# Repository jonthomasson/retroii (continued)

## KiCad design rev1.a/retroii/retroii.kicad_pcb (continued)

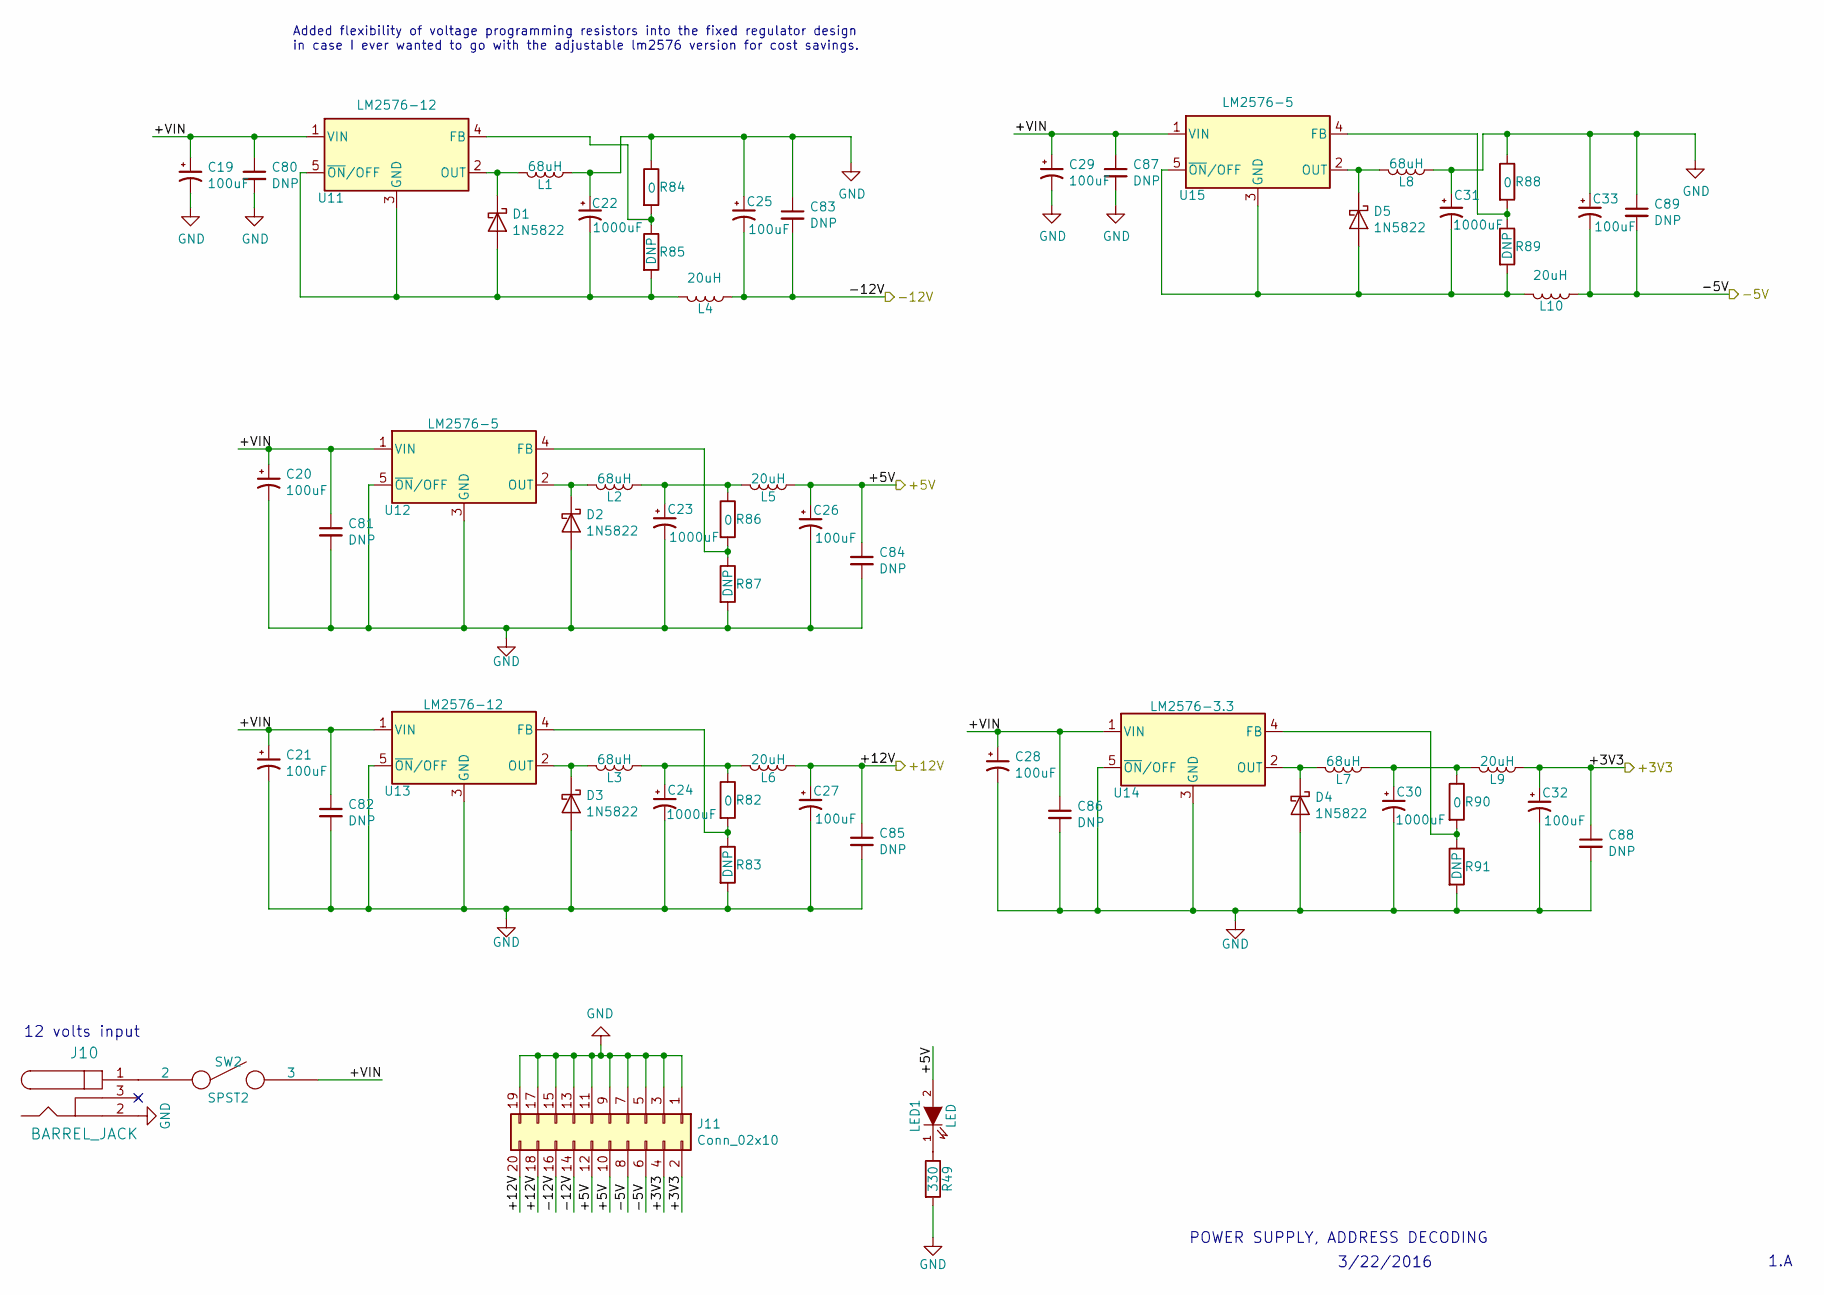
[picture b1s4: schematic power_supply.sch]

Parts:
C19, C20, C21, C25, C26, C27, C28, C29, C32, C33: 100uF; CP_Radial_D8.0mm_P3.50mm
C22, C23, C24, C30, C31: 1000uF; CP_Radial_D13.0mm_P5.00mm
C80, C81, C82, C83, C84, C85, C86, C87, C88, C89: DNP; C_Disc_D3.0mm_W2.0mm_P2.50mm
D1, D2, D3, D4, D5: 1N5822; D_DO-201AD_P15.24mm_Horizontal
J10: BARREL_JACK; Barrel_Jack_PJ002A
J11: Conn_02x10; PinSocket_2x10_P2.54mm_Vertical
L1, L2, L3, L7, L8: 68uH; Bourns_SRP1770TA-101M
L4, L5, L6, L9, L10: 20uH; Pulse_PF0382.223NLT
LED1: LED; WP1503CB_LED
R49: 330; R_Axial_DIN0207_L6.3mm_D2.5mm_P10.16mm_Horizontal
R82, R84, R86, R88, R90: 0; R_Axial_DIN0207_L6.3mm_D2.5mm_P10.16mm_Horizontal
R83, R85, R87, R89, R91: DNP; R_Axial_DIN0207_L6.3mm_D2.5mm_P10.16mm_Horizontal
SW2: SPST2; SW_Micro_Right_Angle_SPST
U11, U13: LM2576-12; TO-220-5_Horizontal_TabDown
U12, U15: LM2576-5; TO-220-5_Horizontal_TabDown
U14: LM2576-3.3; TO-220-5_Horizontal_TabDown

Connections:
/Address_Decoding/+5V: C26.1, C84.1, J11.10, J11.12, L5.1, LED1.2 (A); also elsewhere on the board
/Peripheral_IO/+12V: C27.1, C85.1, J11.18, J11.20, L6.1; also elsewhere on the board
/Peripheral_IO/-5V: C33.2, C89.2, J11.6, J11.8, L10.1; also elsewhere on the board
/Peripheral_IO/-12V: C25.2, C83.2, J11.14, J11.16, L4.1; also elsewhere on the board
/Power_Supply/+3V3: C32.1, C88.1, J11.2, J11.4, L9.1; also elsewhere on the board
/Power_Supply/+VIN: C19.1, C20.1, C21.1, C28.1, C29.1, C80.1, C81.1, C82.1, C86.1, C87.1, SW2.3, U11.1 (VIN), U12.1 (VIN), U13.1 (VIN), U14.1 (VIN), U15.1 (VIN)
GND: C19.2, C20.2, C21.2, C22.1, C23.2, C24.2, C25.1, C26.2, C27.2, C28.2, C29.2, C30.2, C31.1, C32.2, C33.1, C80.2, C81.2, C82.2, C83.1, C84.2, C85.2, C86.2, C87.2, C88.2, C89.1, D2.2 (A), D3.2 (A), D4.2 (A), J10.2, J11.1, J11.3, J11.5, J11.7, J11.9, J11.11, J11.13, J11.15, J11.17, J11.19, L1.1, L8.1, R49.2, R83.2, R84.1, R87.2, R88.1, R91.2, U12.3 (GND), U12.5 (~ON~/OFF), U13.3 (GND), U13.5 (~ON~/OFF), U14.3 (GND), U14.5 (~ON~/OFF); also elsewhere on the board
unnamed: C22.2, D1.2 (A), L4.2, R85.2, U11.3 (GND), U11.5 (~ON~/OFF)
unnamed: C23.1, L2.1, L5.2, R86.1
unnamed: C24.1, L3.1, L6.2, R82.1
unnamed: C30.1, L7.1, L9.2, R90.1
unnamed: C31.2, D5.2 (A), L10.2, R89.2, U15.3 (GND), U15.5 (~ON~/OFF)
unnamed: D1.1 (K), L1.2, U11.2 (OUT)
unnamed: D2.1 (K), L2.2, U12.2 (OUT)
unnamed: D3.1 (K), L3.2, U13.2 (OUT)
unnamed: D4.1 (K), L7.2, U14.2 (OUT)
unnamed: D5.1 (K), L8.2, U15.2 (OUT)
unnamed: LED1.1 (K), R49.1
unnamed: R82.2, R83.1, U13.4 (FB)
unnamed: R84.2, R85.1, U11.4 (FB)
unnamed: R86.2, R87.1, U12.4 (FB)
unnamed: R88.2, R89.1, U15.4 (FB)
unnamed: R90.2, R91.1, U14.4 (FB)

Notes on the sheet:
12 volts input
POWER SUPPLY, ADDRESS DECODING
3/22/2016
1.A
Added flexibility of voltage programming resistors into the fixed regulator design in case I ever wanted to go with the adjustable lm2576 version for cost savings.

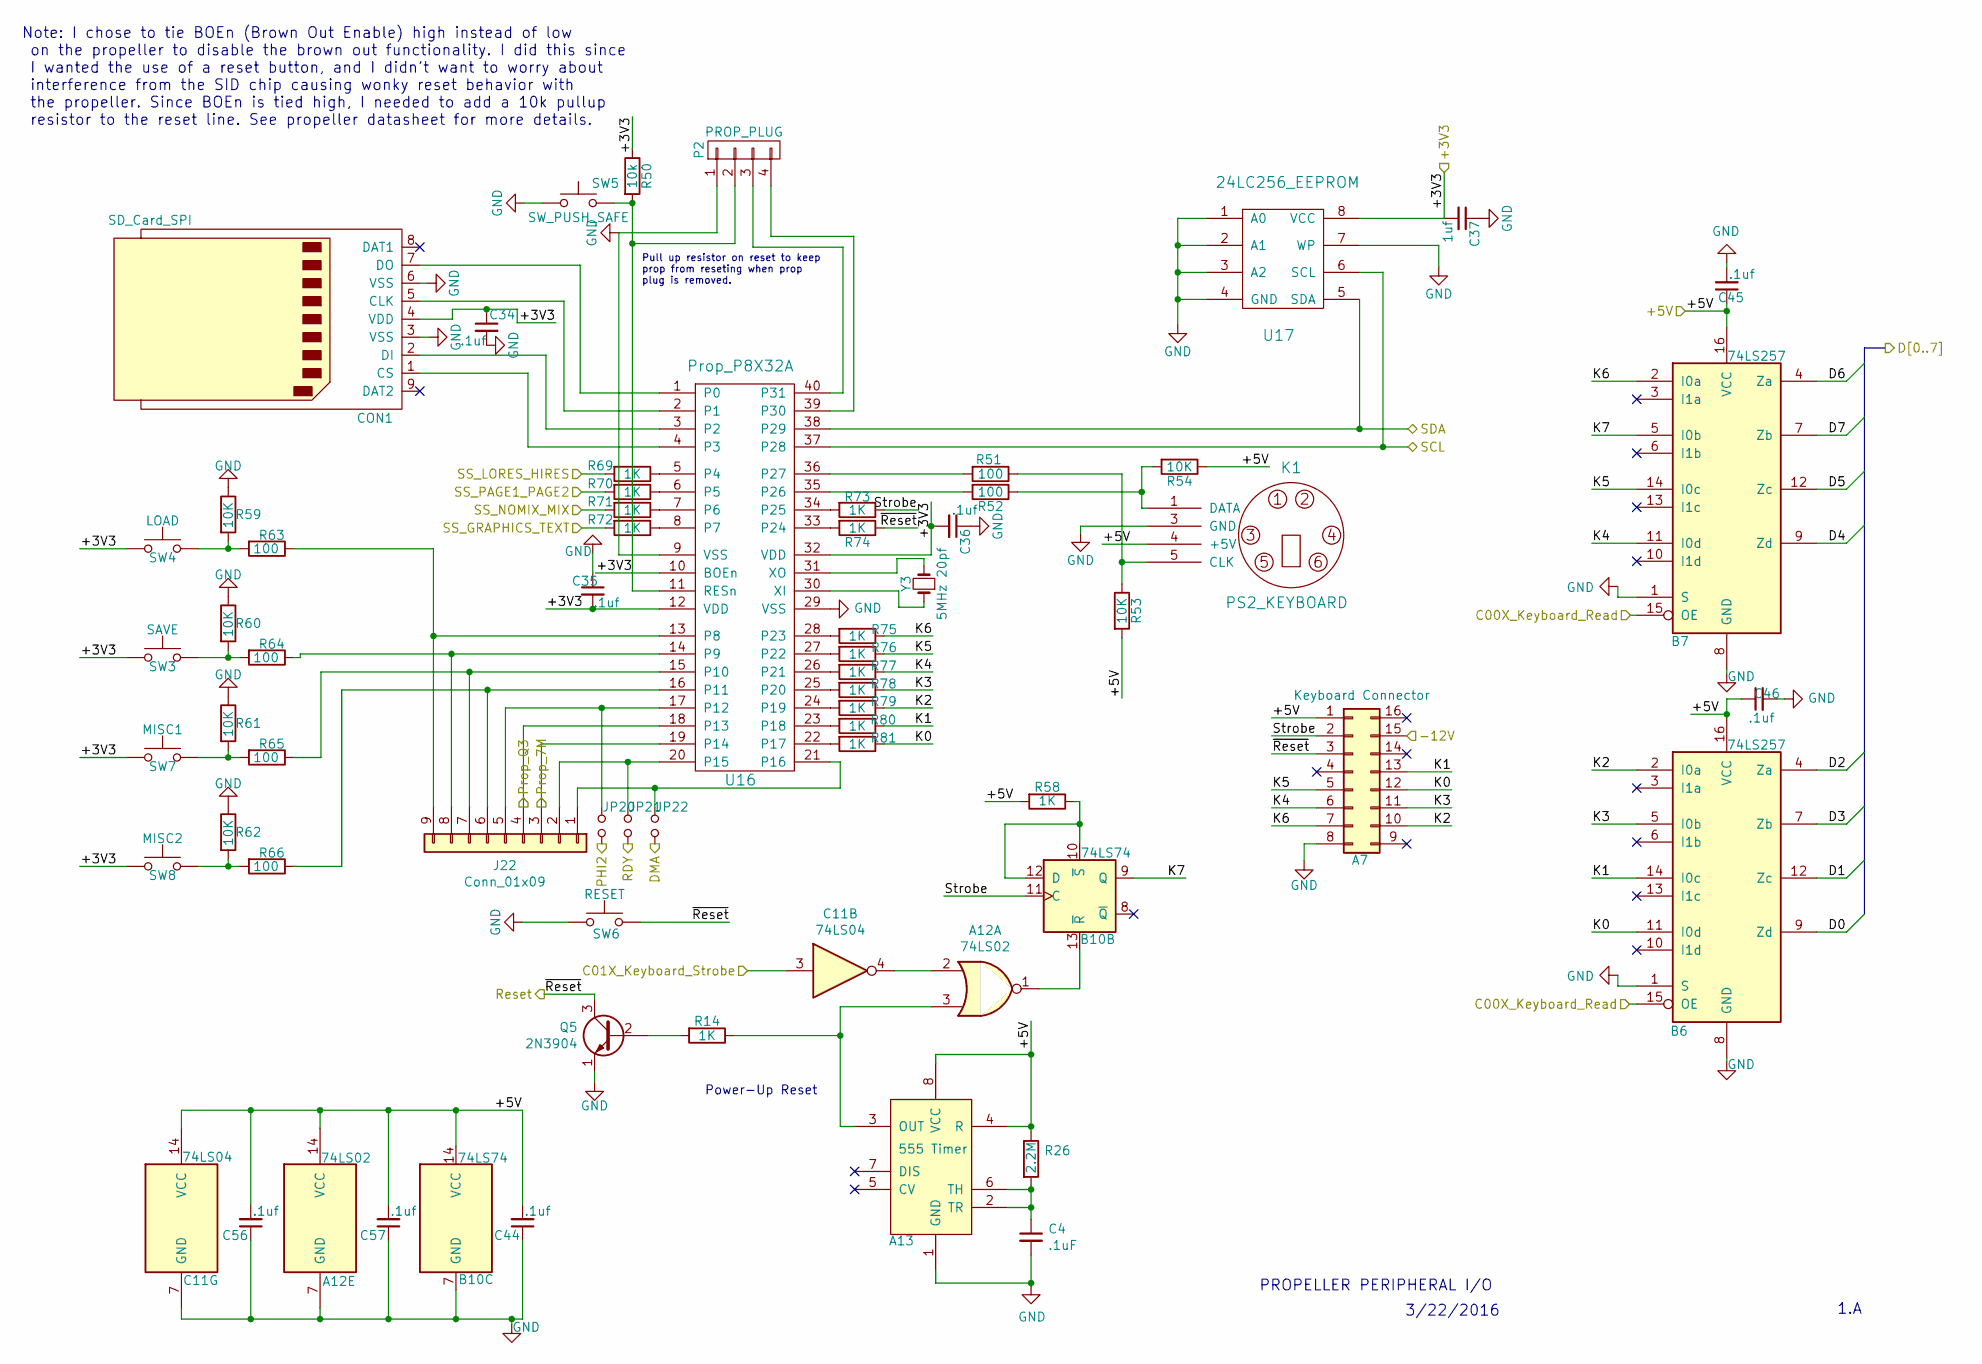
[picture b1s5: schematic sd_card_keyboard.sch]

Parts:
A7: Keyboard Connector; DIP-16_W7.62mm_Socket_LongPads
A12: 74LS02; DIP-14_W7.62mm_Socket_LongPads
A13: 555 Timer; DIP-8_W7.62mm_Socket_LongPads
B6, B7: 74LS257; DIP-16_W7.62mm_Socket_LongPads
B10: 74LS74; DIP-14_W7.62mm_Socket_LongPads
C4: .1uF; C_Disc_D3.0mm_W2.0mm_P2.50mm
C11: 74LS04; DIP-14_W7.62mm_Socket_LongPads
C34, C35, C36, C44, C45, C46, C56, C57: .1uf; C_Disc_D3.0mm_W2.0mm_P2.50mm
C37: 1uf; C_Disc_D4.7mm_W2.5mm_P5.00mm
CON1: SD_Card_SPI; DM1AASFPEJ_SDCARD
J22: Conn_01x09; PinSocket_1x09_P2.54mm_Vertical
JP20, JP21, JP22: Jumper_NO_Small; PinHeader_1x02_P2.54mm_Vertical
K1: PS2_KEYBOARD; MD60SM
P2: PROP_PLUG; PinHeader_1x04_P2.54mm_Vertical
Q5: 2N3904; TO-92_Inline
R14, R58, R69, R70, R71, R72, R73, R74, R75, R76, R77, R78, R79, R80, R81: 1K; R_Axial_DIN0207_L6.3mm_D2.5mm_P10.16mm_Horizontal
R26: 2.2M; R_Axial_DIN0207_L6.3mm_D2.5mm_P10.16mm_Horizontal
R50: 10k; R_Axial_DIN0207_L6.3mm_D2.5mm_P10.16mm_Horizontal
R51, R52, R63, R64, R65, R66: 100; R_Axial_DIN0207_L6.3mm_D2.5mm_P10.16mm_Horizontal
R53, R54, R59, R60, R61, R62: 10K; R_Axial_DIN0207_L6.3mm_D2.5mm_P10.16mm_Horizontal
SW3: SAVE; TE_Tactile_2-1825027-0
SW4: LOAD; TE_Tactile_2-1825027-0
SW5: SW_PUSH_SAFE; TE_1825910-6
SW6: RESET; TE_Tactile_2-1825027-0
SW7: MISC1; TE_Tactile_2-1825027-0
SW8: MISC2; TE_Tactile_2-1825027-0
U16: Prop_P8X32A; DIP-40_W15.24mm_Socket_LongPads
U17: 24LC256_EEPROM; DIP-8_W7.62mm_Socket_LongPads
Y3: 5MHz 20pf; crystal_hc-49s

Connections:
/Address_Decoding/+5V: A7.1, A12.14 (VCC), A13.4 (R), A13.8 (VCC), B6.16 (VCC), B7.16 (VCC), B10.14 (VCC), C11.14 (VCC), C44.2, C45.1, C46.1, C56.2, C57.2, K1.4 (+5V), R26.1, R53.2, R54.1, R58.2; also elsewhere on the board
/Address_Decoding/C00X_Keyboard_Read: B6.15 (OE), B7.15 (OE); also elsewhere on the board
/Address_Decoding/C01X_Keyboard_Strobe: C11.3; also elsewhere on the board
/Address_Decoding/PHI2: JP20.2; also elsewhere on the board
/Address_Decoding/SS_GRAPHICS_TEXT: R72.2; also elsewhere on the board
/Address_Decoding/SS_LORES_HIRES: R69.2; also elsewhere on the board
/Address_Decoding/SS_NOMIX_MIX: R71.2; also elsewhere on the board
/Address_Decoding/SS_PAGE1_PAGE2: R70.2; also elsewhere on the board
/CPU_RAM_ROM/D0: B6.9 (Zd); also elsewhere on the board
/CPU_RAM_ROM/D1: B6.12 (Zc); also elsewhere on the board
/CPU_RAM_ROM/D2: B6.4 (Za); also elsewhere on the board
/CPU_RAM_ROM/D3: B6.7 (Zb); also elsewhere on the board
/CPU_RAM_ROM/D4: B7.9 (Zd); also elsewhere on the board
/CPU_RAM_ROM/D5: B7.12 (Zc); also elsewhere on the board
/CPU_RAM_ROM/D6: B7.4 (Za); also elsewhere on the board
/CPU_RAM_ROM/DMA: JP22.2; also elsewhere on the board
/CPU_RAM_ROM/RDY: JP21.2; also elsewhere on the board
/CPU_RAM_ROM/RESB: A7.3, Q5.3 (C), R74.1, SW6.4; also elsewhere on the board
/Peripheral_IO/-12V: A7.15; also elsewhere on the board
/Peripheral_IO/Prop_7M: J22.3, U16.19 (P14); also elsewhere on the board
/Peripheral_IO/Prop_Q3: J22.4, U16.18 (P13); also elsewhere on the board
/Power_Supply/+3V3: C34.1, C35.2, C36.2, C37.2, CON1.4 (VDD), R50.1, SW3.1, SW4.1, SW7.1, SW8.1, U16.10 (BOEn), U16.12 (VDD), U16.32 (VDD), U17.8 (VCC); also elsewhere on the board
/SD_Card_And_Keyboard/K0: A7.12, B6.11 (I0d), R81.1
/SD_Card_And_Keyboard/K1: A7.13, B6.14 (I0c), R80.1
/SD_Card_And_Keyboard/K2: A7.10, B6.2 (I0a), R79.1
/SD_Card_And_Keyboard/K3: A7.11, B6.5 (I0b), R78.1
/SD_Card_And_Keyboard/K4: A7.6, B7.11 (I0d), R77.1
/SD_Card_And_Keyboard/K5: A7.5, B7.14 (I0c), R76.1
/SD_Card_And_Keyboard/K6: A7.7, B7.2 (I0a), R75.1
/SD_Card_And_Keyboard/K7: B7.5 (I0b), B10.9 (Q)
/SD_Card_And_Keyboard/SCL: U16.37 (P28), U17.6 (SCL); also elsewhere on the board
/SD_Card_And_Keyboard/SDA: U16.38 (P29), U17.5 (SDA); also elsewhere on the board
/SD_Card_And_Keyboard/Strobe: A7.2, B10.11 (C), R73.1
GND: A7.8, A12.7 (GND), A13.1 (GND), B6.1 (S), B6.8 (GND), B7.1 (S), B7.8 (GND), B10.7 (GND), C4.2, C11.7 (GND), C34.2, C35.1, C36.1, C37.1, C44.1, C45.2, C46.2, C56.1, C57.1, CON1.3 (VSS), CON1.6 (VSS), K1.3 (GND), P2.1, Q5.1 (E), R59.1, R60.1, R61.1, R62.1, SW5.1, SW6.1, U16.9 (VSS), U16.29 (VSS), U17.1 (A0), U17.2 (A1), U17.3 (A2), U17.4 (GND), U17.7 (WP); also elsewhere on the board
unnamed: A12.1, B10.13 (~R)
unnamed: A12.2, C11.4
unnamed: A12.3, A13.3 (OUT), R14.1
unnamed: A13.2 (TR), A13.6 (TH), C4.1, R26.2
unnamed: B10.10 (~S), B10.12 (D), R58.1
unnamed: CON1.1 (CS), U16.4 (P3)
unnamed: CON1.2 (DI), U16.3 (P2)
unnamed: CON1.5 (CLK), U16.2 (P1)
unnamed: CON1.7 (DO), U16.1 (P0)
unnamed: J22.1, JP22.1, U16.21 (P16)
unnamed: J22.2, JP21.1, U16.20 (P15)
unnamed: J22.5, JP20.1, U16.17 (P12)
unnamed: J22.6, R66.1, U16.16 (P11)
unnamed: J22.7, R65.1, U16.15 (P10)
unnamed: J22.8, R64.1, U16.14 (P9)
unnamed: J22.9, R63.1, U16.13 (P8)
unnamed: K1.1 (DATA), R52.1, R54.2
unnamed: K1.5 (CLK), R51.1, R53.1
unnamed: P2.2, R50.2, SW5.4, U16.11 (RESn)
unnamed: P2.3, U16.40 (P31)
unnamed: P2.4, U16.39 (P30)
unnamed: Q5.2 (B), R14.2
unnamed: R51.2, U16.36 (P27)
unnamed: R52.2, U16.35 (P26)
unnamed: R59.2, R63.2, SW4.4
unnamed: R60.2, R64.2, SW3.4
unnamed: R61.2, R65.2, SW7.4
unnamed: R62.2, R66.2, SW8.4
unnamed: R69.1, U16.5 (P4)
unnamed: R70.1, U16.6 (P5)
unnamed: R71.1, U16.7 (P6)
unnamed: R72.1, U16.8 (P7)
unnamed: R73.2, U16.34 (P25)
unnamed: R74.2, U16.33 (P24)
unnamed: R75.2, U16.28 (P23)
unnamed: R76.2, U16.27 (P22)
unnamed: R77.2, U16.26 (P21)
unnamed: R78.2, U16.25 (P20)
unnamed: R79.2, U16.24 (P19)
unnamed: R80.2, U16.23 (P18)
unnamed: R81.2, U16.22 (P17)
unnamed: U16.30 (XI), Y3.1
unnamed: U16.31 (XO), Y3.2

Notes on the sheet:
Note: I chose to tie BOEn (Brown Out Enable) high instead of low on the propeller to disable the brown out functionality. I did this since I wanted the use of a reset button, and I didn't want to worry about interference from the SID chip causing wonky reset behavior with the propeller. Since BOEn 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
Pull up resistor on reset to keep prop from reseting when prop plug is removed.
PROPELLER PERIPHERAL I/O
3/22/2016
1.A
Power-Up Reset

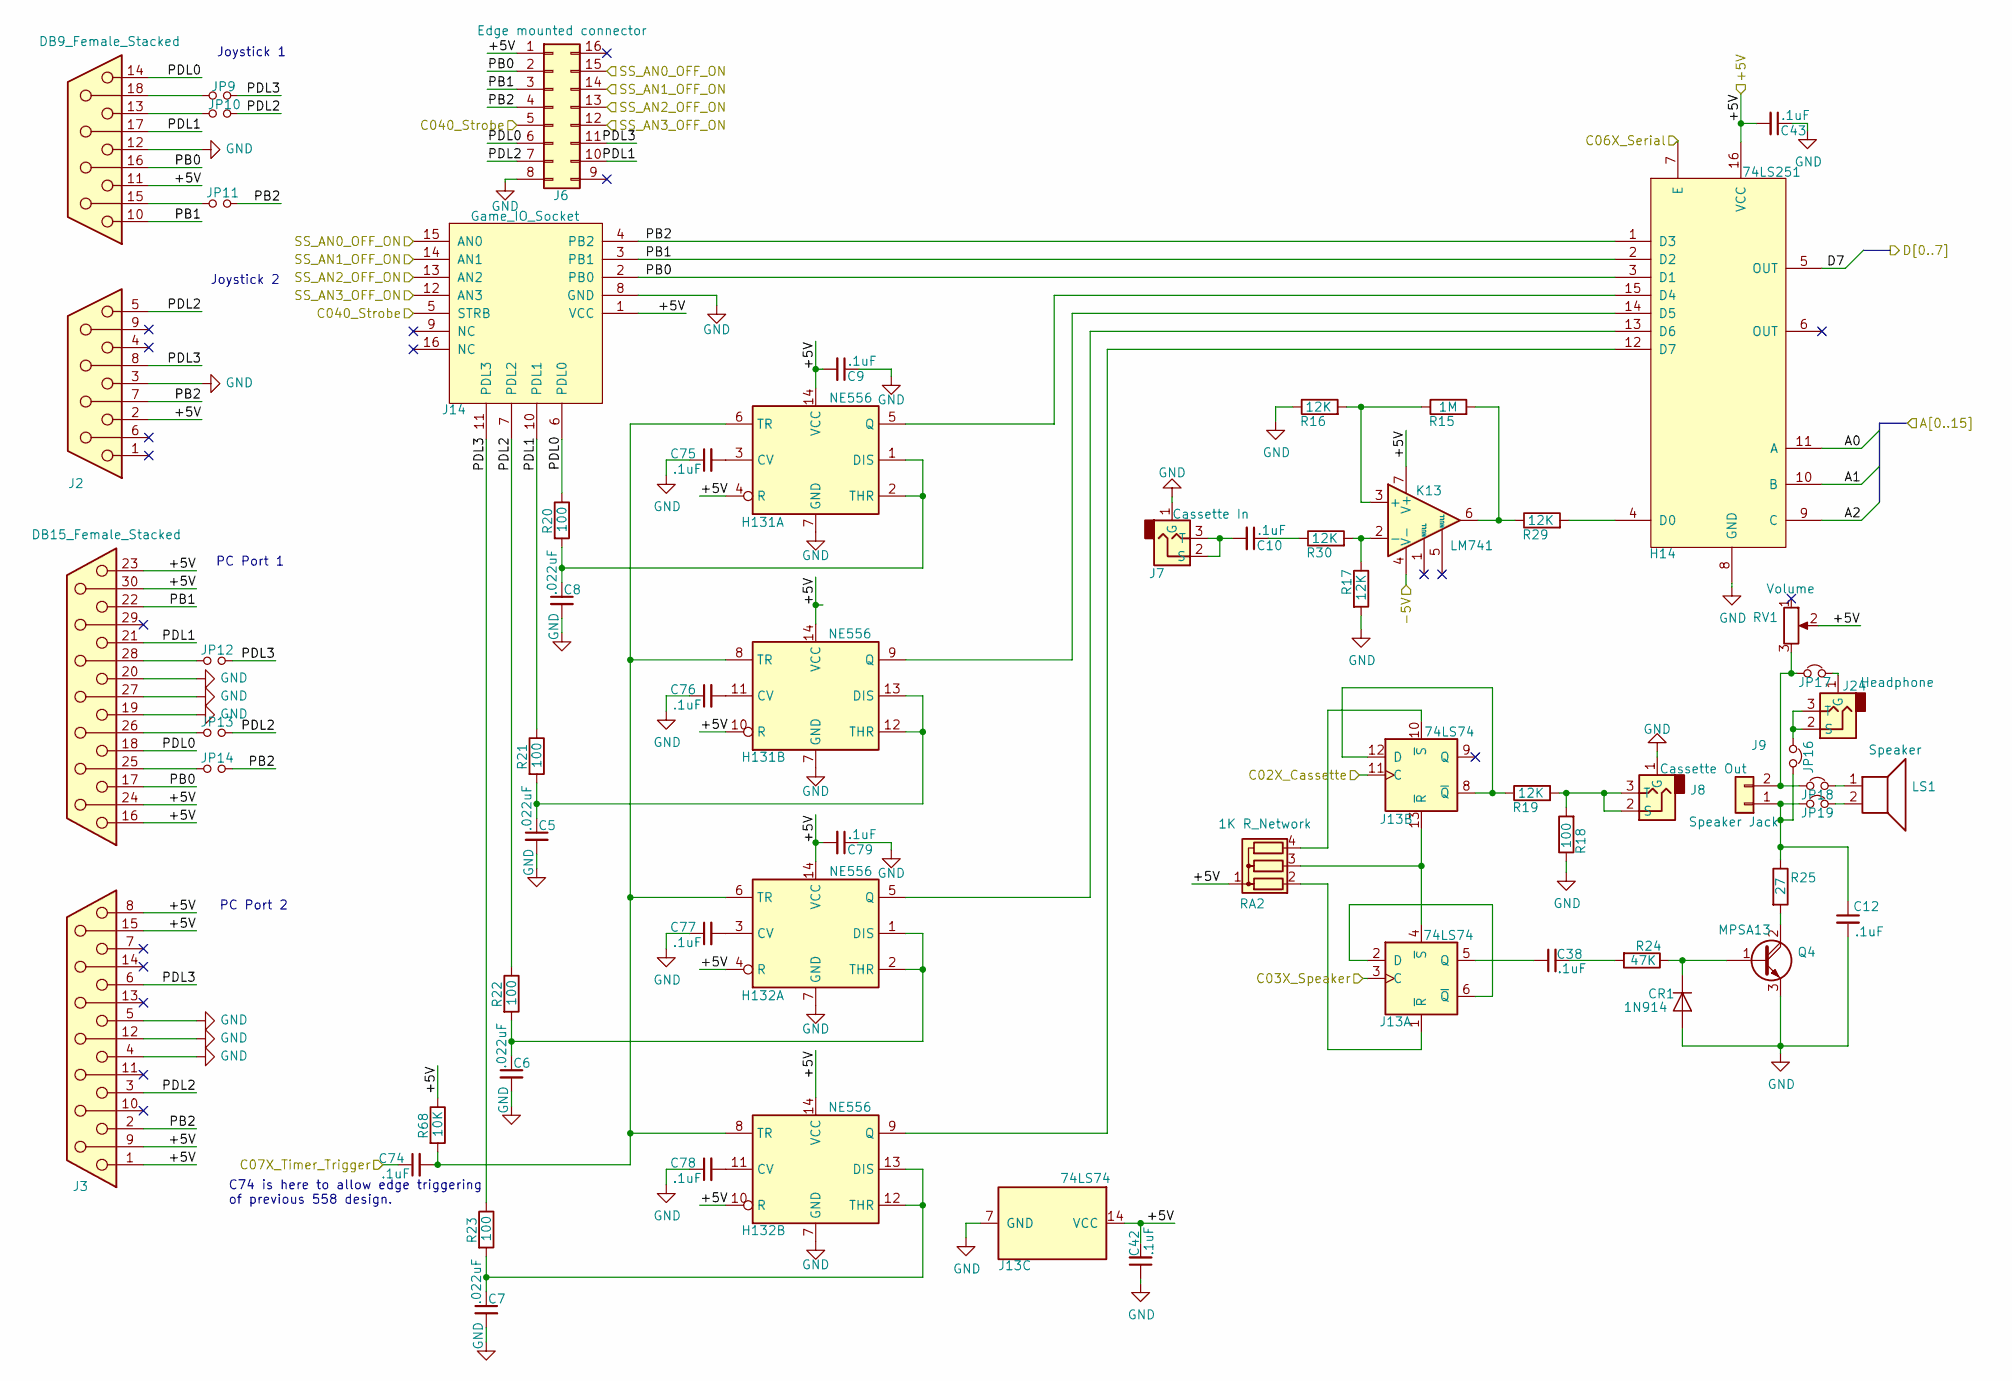
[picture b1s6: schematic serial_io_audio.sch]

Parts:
C5, C6, C7, C8: .022uF; C_Disc_D3.4mm_W2.1mm_P2.50mm
C9, C10, C12, C38, C42, C43, C74, C75, C76, C77, C78, C79: .1uF; C_Disc_D3.0mm_W2.0mm_P2.50mm
CR1: 1N914; D_DO-35_SOD27_P7.62mm_Horizontal
H14: 74LS251; DIP-16_W7.62mm_Socket_LongPads
H131, H132: NE556; DIP-14_W7.62mm_Socket_LongPads
J2: DB9_Female_Stacked; Amphenol_L17H2220131
J3: DB15_Female_Stacked; Amphenol_L17H2440131
J6: Edge mounted connector; PinSocket_2x08_P2.54mm_Vertical
J7: Cassette In; SJ13525NHeadphone
J8: Cassette Out; SJ13525NHeadphone
J9: Speaker Jack; PinSocket_1x02_P2.54mm_Vertical
J13: 74LS74; DIP-14_W7.62mm_Socket_LongPads
J14: Game_IO_Socket; DIP-16_W7.62mm_Socket_LongPads
J24: Headphone; SJ13525NHeadphone
JP9, JP10, JP11, JP12, JP13, JP14: Jumper_NO_Small; PinHeader_1x02_P2.54mm_Vertical
JP16, JP17, JP18, JP19: Jumper_NC_Small; PinHeader_1x02_P2.54mm_Vertical
K13: LM741; DIP-8_W7.62mm_Socket_LongPads
LS1: Speaker; CUI_CVI_1708
Q4: MPSA13; TO-92_Inline
R15: 1M; R_Axial_DIN0207_L6.3mm_D2.5mm_P10.16mm_Horizontal
R16, R17, R19, R29, R30: 12K; R_Axial_DIN0207_L6.3mm_D2.5mm_P10.16mm_Horizontal
R18, R20, R21, R22, R23: 100; R_Axial_DIN0207_L6.3mm_D2.5mm_P10.16mm_Horizontal
R24: 47K; R_Axial_DIN0207_L6.3mm_D2.5mm_P10.16mm_Horizontal
R25: 27; R_Axial_DIN0207_L6.3mm_D2.5mm_P10.16mm_Horizontal
R68: 10K; R_Axial_DIN0207_L6.3mm_D2.5mm_P10.16mm_Horizontal
RA2: 1K R_Network; R_Array_SIP4
RV1: Volume; BOURNS_91A1A-B24-D15L

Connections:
/Address_Decoding/+5V: C9.2, C42.2, C43.2, C79.2, H14.16 (VCC), H131.4 (R), H131.10 (R), H131.14 (VCC), H132.4 (R), H132.10 (R), H132.14 (VCC), J2.2, J2.11, J3.1, J3.8, J3.9, J3.15, J3.16, J3.23, J3.24, J3.30, J6.1, J13.14 (VCC), J14.1 (VCC), K13.7 (V+), R68.1, RA2.1 (common), RV1.2; also elsewhere on the board
/Address_Decoding/A0: H14.11 (A); also elsewhere on the board
/Address_Decoding/A1: H14.10 (B); also elsewhere on the board
/Address_Decoding/A2: H14.9 (C); also elsewhere on the board
/Address_Decoding/C02X_Cassette: J13.11 (C); also elsewhere on the board
/Address_Decoding/C03X_Speaker: J13.3 (C); also elsewhere on the board
/Address_Decoding/C06X_Serial: H14.7 (E); also elsewhere on the board
/Address_Decoding/C07X_Timer_Trigger: C74.1; also elsewhere on the board
/Address_Decoding/C040_Strobe: J6.5, J14.5 (STRB); also elsewhere on the board
/Address_Decoding/SS_AN0_OFF_ON: J6.15, J14.15 (AN0); also elsewhere on the board
/Address_Decoding/SS_AN1_OFF_ON: J6.14, J14.14 (AN1); also elsewhere on the board
/Address_Decoding/SS_AN2_OFF_ON: J6.13, J14.13 (AN2); also elsewhere on the board
/Address_Decoding/SS_AN3_OFF_ON: J6.12, J14.12 (AN3); also elsewhere on the board
/Peripheral_IO/-5V: K13.4 (V-); also elsewhere on the board
/Serial_IO_Audio/PB0: H14.3 (D1), J2.16, J3.17, J6.2, J14.2 (PB0)
/Serial_IO_Audio/PB1: H14.2 (D2), J2.10, J3.22, J6.3, J14.3 (PB1)
/Serial_IO_Audio/PB2: H14.1 (D3), J2.7, J3.2, J6.4, J14.4 (PB2), JP11.2, JP14.2
/Serial_IO_Audio/PDL0: J2.14, J3.18, J6.6, J14.6 (PDL0), R20.1
/Serial_IO_Audio/PDL1: J2.17, J3.21, J6.10, J14.10 (PDL1), R21.1
/Serial_IO_Audio/PDL2: J2.5, J3.3, J6.7, J14.7 (PDL2), JP10.2, JP13.2, R22.1
/Serial_IO_Audio/PDL3: J2.8, J3.6, J6.11, J14.11 (PDL3), JP9.2, JP12.2, R23.1
GND: C5.2, C6.2, C7.2, C8.2, C9.1, C12.2, C42.1, C43.1, C75.1, C76.1, C77.1, C78.1, C79.1, CR1.2 (A), H14.8 (GND), H131.7 (GND), H132.7 (GND), J2.3, J2.12, J3.4, J3.5, J3.12, J3.19, J3.20, J3.27, J6.8, J7.1 (G), J8.1 (G), J13.7 (GND), J14.8 (GND), Q4.3 (E), R16.1, R17.2, R18.1; also elsewhere on the board
unnamed: C5.1, H131.12 (THR), H131.13 (DIS), R21.2
unnamed: C6.1, H132.1 (DIS), H132.2 (THR), R22.2
unnamed: C7.1, H132.12 (THR), H132.13 (DIS), R23.2
unnamed: C8.1, H131.1 (DIS), H131.2 (THR), R20.2
unnamed: C10.1, R30.1
unnamed: C10.2, J7.2 (S), J7.3 (T)
unnamed: C12.1, J9.1, JP16.2, JP19.1, R25.1
unnamed: C38.1, J13.5 (Q)
unnamed: C38.2, R24.2
unnamed: C74.2, H131.6 (TR), H131.8 (TR), H132.6 (TR), H132.8 (TR), R68.2
unnamed: C75.2, H131.3 (CV)
unnamed: C76.2, H131.11 (CV)
unnamed: C77.2, H132.3 (CV)
unnamed: C78.2, H132.11 (CV)
unnamed: CR1.1 (K), Q4.1 (B), R24.1
unnamed: H14.4 (D0), R29.2
unnamed: H14.15 (D4), H131.5 (Q)
unnamed: H14.14 (D5), H131.9 (Q)
unnamed: H14.13 (D6), H132.5 (Q)
unnamed: H14.12 (D7), H132.9 (Q)
unnamed: J2.13, JP10.1
unnamed: J2.15, JP11.1
unnamed: J2.18, JP9.1
unnamed: J3.25, JP14.1
unnamed: J3.26, JP13.1
unnamed: J3.28, JP12.1
unnamed: J8.2 (S), J8.3 (T), R18.2, R19.2
unnamed: J9.2, JP17.1, JP18.1, RV1.3
unnamed: J13.1 (~R), RA2.2 (R1)
unnamed: J13.2 (D), J13.6 (~Q)
unnamed: J13.10 (~S), RA2.4 (R3)
unnamed: J13.8 (~Q), J13.12 (D), R19.1
unnamed: J13.4 (~S), J13.13 (~R), RA2.3 (R2)
unnamed: J24.1 (G), JP17.2
unnamed: J24.2 (S), J24.3 (T), JP16.1
unnamed: JP18.2, LS1.1
unnamed: JP19.2, LS1.2
unnamed: K13.2 (-), R17.1, R30.2
unnamed: K13.3 (+), R15.1, R16.2
unnamed: K13.6, R15.2, R29.1
unnamed: Q4.2 (C), R25.2

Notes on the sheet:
C74 is here to allow edge triggering of previous 558 design.
Joystick 1
Joystick 2
PC Port 1
PC Port 2

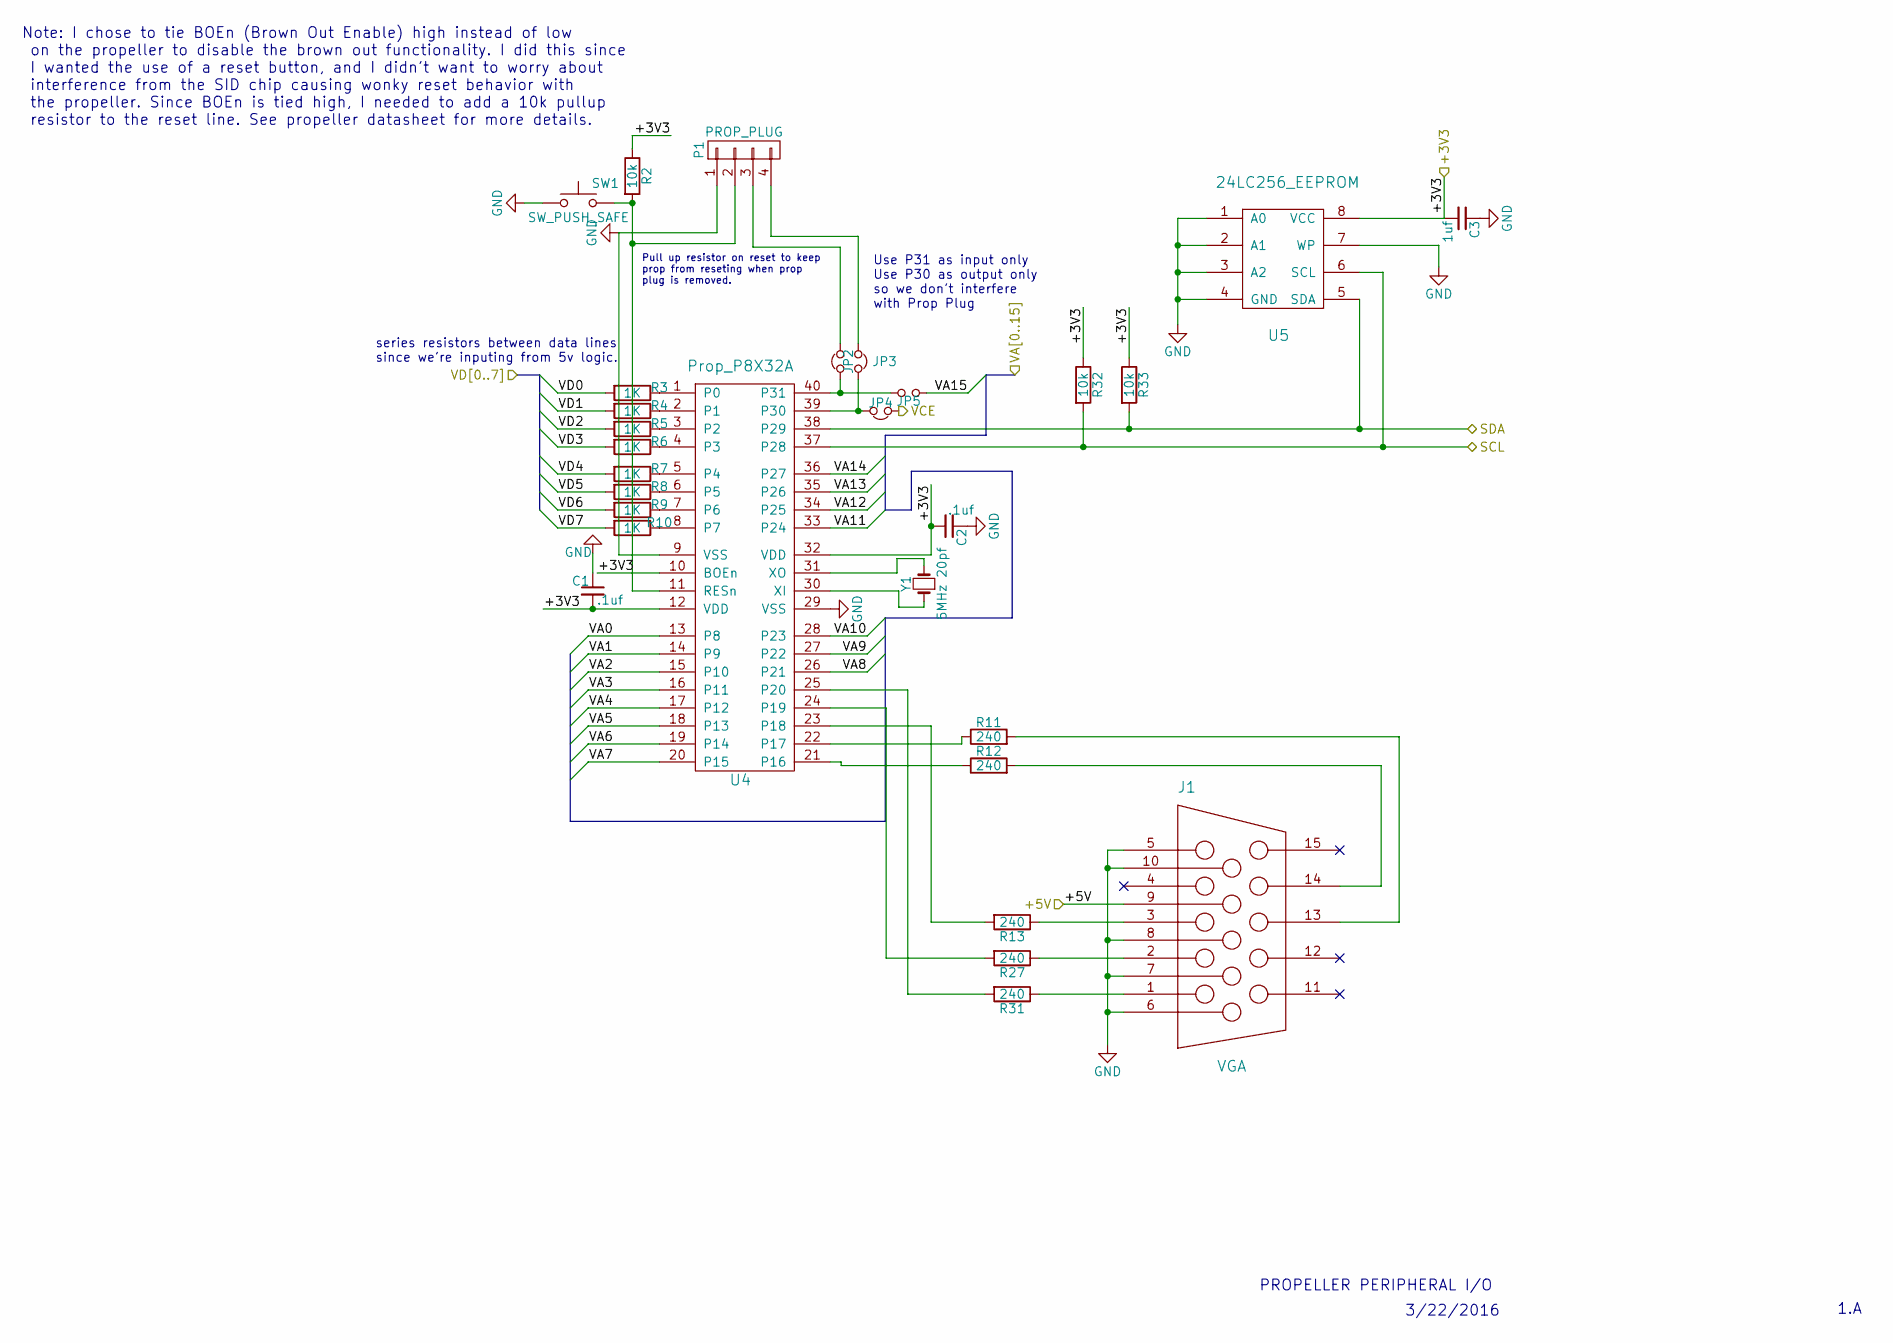
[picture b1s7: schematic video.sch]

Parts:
C1, C2: .1uf; C_Disc_D3.0mm_W2.0mm_P2.50mm
C3: 1uf; C_Disc_D4.7mm_W2.5mm_P5.00mm
J1: VGA; Amphenol_ICD15S13E6GV00LF
JP2, JP3, JP4, JP5: Jumper_NO_Small; PinHeader_1x02_P2.54mm_Vertical
P1: PROP_PLUG; PinHeader_1x04_P2.54mm_Vertical
R2, R32, R33: 10k; R_Axial_DIN0207_L6.3mm_D2.5mm_P10.16mm_Horizontal
R3, R4, R5, R6, R7, R8, R9, R10: 1K; R_Axial_DIN0207_L6.3mm_D2.5mm_P10.16mm_Horizontal
R11, R12, R13, R27, R31: 240; R_Axial_DIN0207_L6.3mm_D2.5mm_P10.16mm_Horizontal
SW1: SW_PUSH_SAFE; TE_1825910-6
U4: Prop_P8X32A; DIP-40_W15.24mm_Socket_LongPads
U5: 24LC256_EEPROM; DIP-8_W7.62mm_Socket_LongPads
Y1: 5MHz 20pf; crystal_hc-49s

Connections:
/Address_Decoding/+5V: J1.9 (KEY/PWR); also elsewhere on the board
/CPU_RAM_ROM/VA0: U4.13 (P8); also elsewhere on the board
/CPU_RAM_ROM/VA1: U4.14 (P9); also elsewhere on the board
/CPU_RAM_ROM/VA2: U4.15 (P10); also elsewhere on the board
/CPU_RAM_ROM/VA3: U4.16 (P11); also elsewhere on the board
/CPU_RAM_ROM/VA4: U4.17 (P12); also elsewhere on the board
/CPU_RAM_ROM/VA5: U4.18 (P13); also elsewhere on the board
/CPU_RAM_ROM/VA6: U4.19 (P14); also elsewhere on the board
/CPU_RAM_ROM/VA7: U4.20 (P15); also elsewhere on the board
/CPU_RAM_ROM/VA8: U4.26 (P21); also elsewhere on the board
/CPU_RAM_ROM/VA9: U4.27 (P22); also elsewhere on the board
/CPU_RAM_ROM/VA10: U4.28 (P23); also elsewhere on the board
/CPU_RAM_ROM/VA11: U4.33 (P24); also elsewhere on the board
/CPU_RAM_ROM/VA12: U4.34 (P25); also elsewhere on the board
/CPU_RAM_ROM/VA13: U4.35 (P26); also elsewhere on the board
/CPU_RAM_ROM/VA14: U4.36 (P27); also elsewhere on the board
/CPU_RAM_ROM/VA15: JP5.2; also elsewhere on the board
/CPU_RAM_ROM/VCE: JP4.1; also elsewhere on the board
/CPU_RAM_ROM/VD0: R3.2; also elsewhere on the board
/CPU_RAM_ROM/VD1: R4.2; also elsewhere on the board
/CPU_RAM_ROM/VD2: R5.2; also elsewhere on the board
/CPU_RAM_ROM/VD3: R6.2; also elsewhere on the board
/CPU_RAM_ROM/VD4: R7.2; also elsewhere on the board
/CPU_RAM_ROM/VD5: R8.2; also elsewhere on the board
/CPU_RAM_ROM/VD6: R9.2; also elsewhere on the board
/CPU_RAM_ROM/VD7: R10.2; also elsewhere on the board
/Power_Supply/+3V3: C1.2, C2.2, C3.2, R2.1, R32.1, R33.1, U4.10 (BOEn), U4.12 (VDD), U4.32 (VDD), U5.8 (VCC); also elsewhere on the board
/SD_Card_And_Keyboard/SCL: R32.2, U4.37 (P28), U5.6 (SCL); also elsewhere on the board
/SD_Card_And_Keyboard/SDA: R33.2, U4.38 (P29), U5.5 (SDA); also elsewhere on the board
GND: C1.1, C2.1, C3.1, J1.5 (GND_HSYNC), J1.6 (RED_RTN), J1.7 (GREEN_RTN), J1.8 (BLUE_RTN), J1.10 (GND_VSYNC), P1.1, SW1.1, U4.9 (VSS), U4.29 (VSS), U5.1 (A0), U5.2 (A1), U5.3 (A2), U5.4 (GND), U5.7 (WP); also elsewhere on the board
unnamed: J1.1 (RED), R31.1
unnamed: J1.2 (GREEN), R27.1
unnamed: J1.3 (BLUE), R13.1
unnamed: J1.13 (HSYNC), R11.2
unnamed: J1.14 (VSYNC), R12.2
unnamed: JP2.1, JP5.1, U4.40 (P31)
unnamed: JP2.2, P1.3
unnamed: JP3.1, P1.4
unnamed: JP3.2, JP4.2, U4.39 (P30)
unnamed: P1.2, R2.2, SW1.4, U4.11 (RESn)
unnamed: R3.1, U4.1 (P0)
unnamed: R4.1, U4.2 (P1)
unnamed: R5.1, U4.3 (P2)
unnamed: R6.1, U4.4 (P3)
unnamed: R7.1, U4.5 (P4)
unnamed: R8.1, U4.6 (P5)
unnamed: R9.1, U4.7 (P6)
unnamed: R10.1, U4.8 (P7)
unnamed: R11.1, U4.22 (P17)
unnamed: R12.1, U4.21 (P16)
unnamed: R13.2, U4.23 (P18)
unnamed: R27.2, U4.24 (P19)
unnamed: R31.2, U4.25 (P20)
unnamed: U4.30 (XI), Y1.1
unnamed: U4.31 (XO), Y1.2

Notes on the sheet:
Note: I chose to tie BOEn (Brown Out Enable) high instead of low on the propeller to disable the brown out functionality. I did this since I wanted the use of a reset button, and I didn't want to worry about interference from the SID chip causing wonky reset behavior with the propeller. Since BOEn 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
Pull up resistor on reset to keep prop from reseting when prop plug is removed.
PROPELLER PERIPHERAL I/O
3/22/2016
1.A
Use P31 as input only Use P30 as output only so we don't interfere with Prop Plug
series resistors between data lines since we're inputing from 5v logic.

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
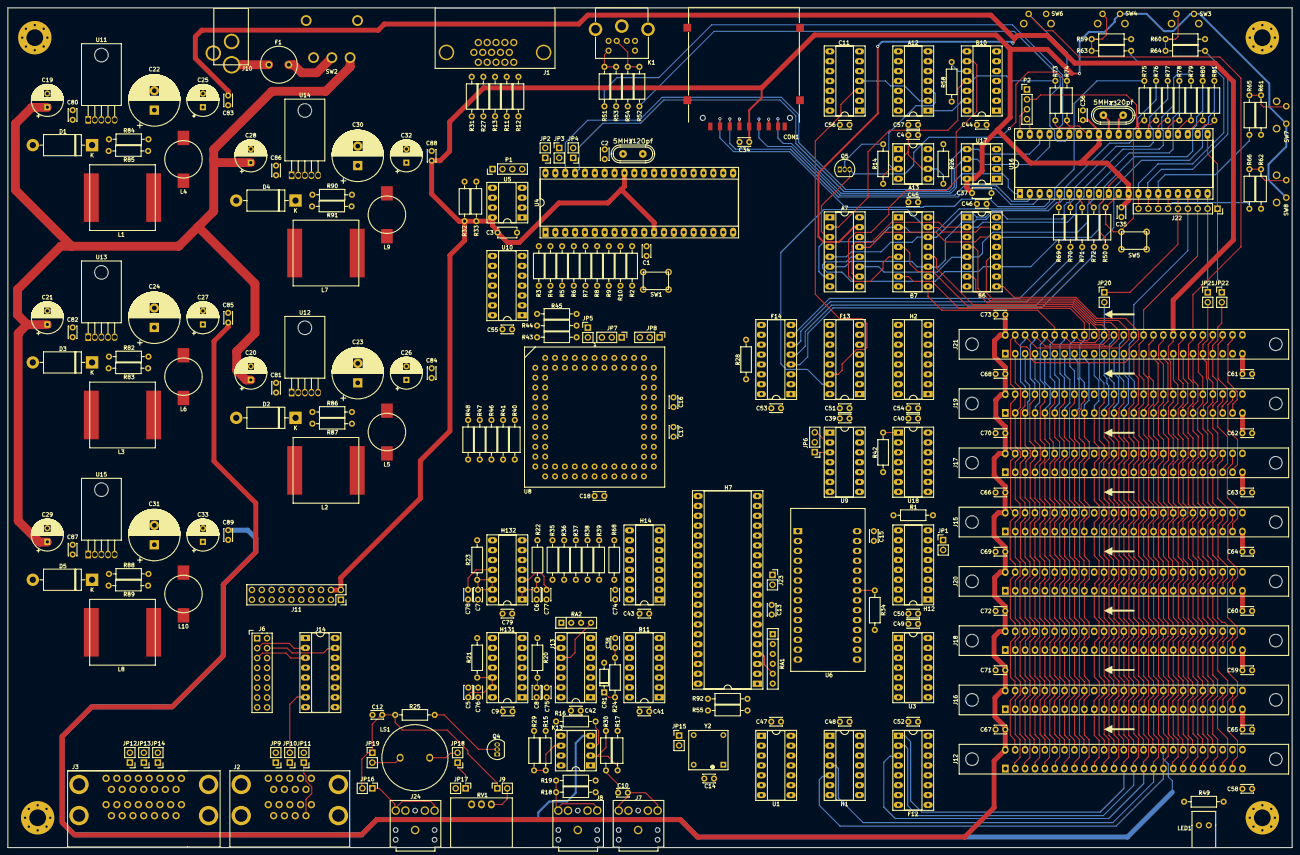
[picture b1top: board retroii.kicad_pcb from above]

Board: 4 copper layers, 330.2 x 215.9 mm, 299 parts (0 on the bottom side), 305 nets.

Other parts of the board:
F1: Fuse 2.5 amp; littlefuse_5.08_radial
H3, H4, H5, H6: MountingHole; MountingHole_4.3mm_M4_Pad_Via
